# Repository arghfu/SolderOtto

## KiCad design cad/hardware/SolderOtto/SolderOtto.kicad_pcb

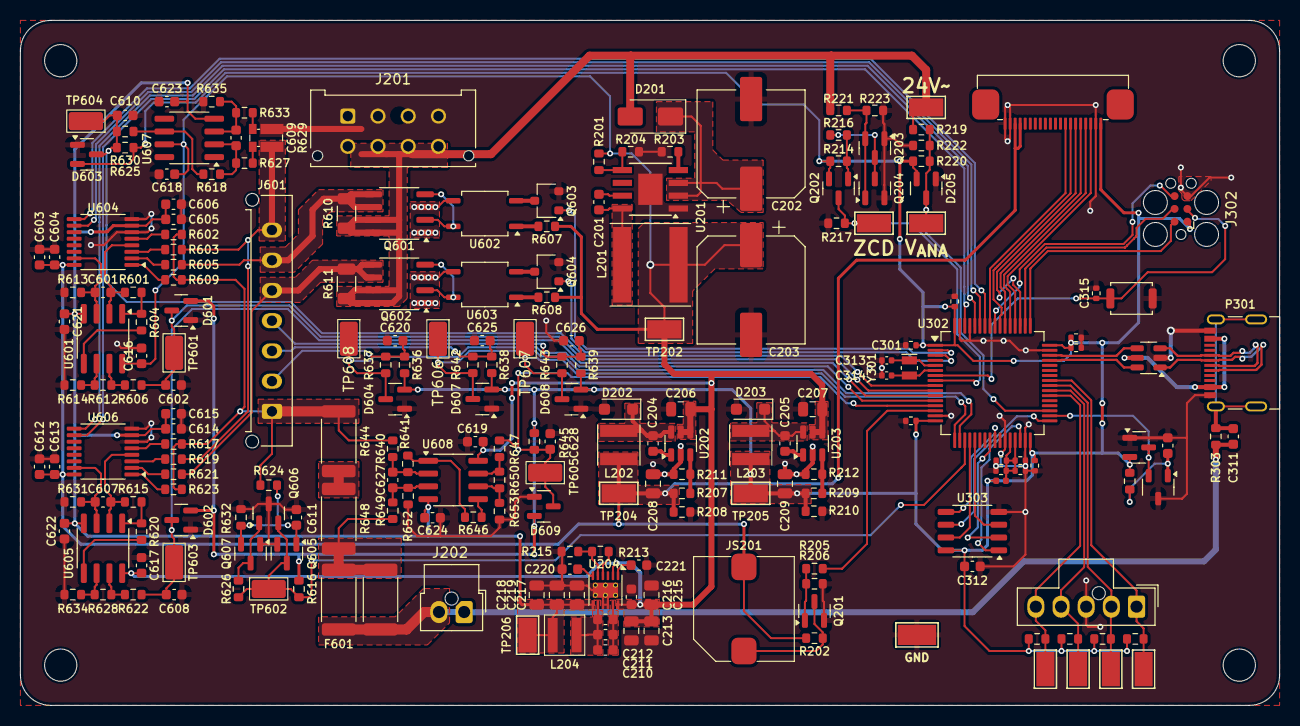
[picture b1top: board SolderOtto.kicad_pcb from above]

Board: 2 copper layers, 125.0 x 68.0 mm, 221 parts (0 on the bottom side), 127 nets.

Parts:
C201, C312, C603, C606, C612, C615, C616, C617, C618, C619, C620, C621, C622, C623, C624, C625, C626: 100n; C_0603_1608Metric
C202, C203: 100u; CP_Elec_10x10.5_A768
C204, C205, C311: 10n; C_0603_1608Metric
C206, C207: 10u; C_0805_2012Metric
C208, C209, C213, C214, C215, C217, C218, C219: 22u; C_0805_2012Metric
C210, C211, C212: 10u; C_0603_1608Metric
C216: 2u2; C_0603_1608Metric
C220, C222, C604, C605, C613, C614: 1u; C_0603_1608Metric
C221: 220n; C_0603_1608Metric
C301, C302, C303, C304, C305, C310, C315: 100n; R_0402_1005Metric
C306: 4u7; R_0402_1005Metric
C307: 10n; R_0402_1005Metric
C308, C309: 1u; R_0402_1005Metric
C313, C314: 9p; C_0402_1005Metric
C601, C607, C609, C627: 47p; C_0603_1608Metric
C602, C608, C610, C628: 1n; C_0603_1608Metric
C611: 100p; C_0603_1608Metric
D201: STPS2H100A; D_SMA
D202, D203: SMD16PL-TP; D_SOD-123F
D204, D205, D601, D602, D603, D604, D607, D608, D609: BAT54SFILM; SOT-23
F601: 1.25A; R_2512_6332Metric
J201: Conn_02x04_Counter_Clockwise; Molex_Micro-Fit_3.0_43045-0812_2x04_P3.00mm_Vertical
J202: Conn_01x02; Molex_Nano-Fit_105309-xx02_1x02_P2.50mm_Vertical
J302: Conn_ARM_SWD_TagConnect_TC2030; Tag-Connect_TC2030-IDC-FP_2x03_P1.27mm_Vertical
J401: Conn_01x20; FPC_BOTTOM_20POS_Würth_68712014522
J501: Conn_01x05; Molex_Nano-Fit_105309-xx05_1x05_P2.50mm_Vertical
J601: Conn_01x07; Molex_Micro-Fit_3.0_43650-0715_1x07_P3.00mm_Vertical
JS201: SMI-1027-T-5V-R
L201: 33u; L_Taiyo-Yuden_NR-80xx
L202, L203: 3u3; L_Taiyo-Yuden_NR-40xx
L204: 2u2; XFL4020
L301: 600R@100MHz; L_0402_1005Metric
P301: USB_C_Plug_USB2.0; USB_C_Receptacle_Molex_C_24P_SMD_RA
Q201: T2N7002AK; SOT-23
Q202, Q606: BC858B; SOT-23
Q203, Q204, Q605, Q607: BC847A; SOT-23
Q601, Q602: Q_Dual_NMOS; SO-8_3.9x4.9mm_P1.27mm
Q603, Q604: DTD123EK; SC-59
R201, R220, R222: 100k; R_0603_1608Metric
R202, R206, R501, R502, R503, R504, R636, R637, R638, R639, R642, R643: 4k7; R_0603_1608Metric
R203: 25k5; R_0603_1608Metric
R204: 14k3; R_0603_1608Metric
R205: 100; R_0603_1608Metric
R207, R209: 49k9; R_0603_1608Metric
R208, R210: 1k; R_0603_1608Metric
R211: 9k53; R_0603_1608Metric
R212: 16k2; R_0603_1608Metric
R213: 130k; R_0603_1608Metric
R214, R216, R217, R616, R646, R653: 10k; R_0603_1608Metric
R215: 24k; R_0603_1608Metric
R218: 200; R_0603_1608Metric
R219: 1M15; R_0603_1608Metric
R221: 22k; R_0603_1608Metric
R223, R303: 1M; R_0603_1608Metric
R601, R613, R615, R631: 590k; R_0603_1608Metric
R602, R603, R605, R609, R612, R617, R619, R621, R623, R628: 22k6; R_0603_1608Metric
R604, R614, R620, R634: 2k7; R_0603_1608Metric
R606, R622: 2k2; R_0603_1608Metric
R607, R608: 470; R_0603_1608Metric
R610, R611: 10M; R_1206_3216Metric
R618, R635: 453k; R_0603_1608Metric
R624: 470k; R_0603_1608Metric
R625, R630, R645, R647: 3k3; R_0603_1608Metric
R626, R632: 47k; R_0603_1608Metric
R627, R633: 20k; R_0603_1608Metric
R629: 5m; R_Shunt_Vishay_WSKW0612
R640, R649: 4k75; R_0603_1608Metric
R641, R652: 200k; R_0603_1608Metric
R644, R648: 220m; R_2512_6332Metric
R650: 187k; R_0603_1608Metric
R651: 1M; R_2512_6332Metric
SW301: SW_Push; SW_Push_SPST_NO_Alps_SKRK
TP201: 24V~; TestPoint_Keystone_5015_Micro-Minature
TP202: 12V; TestPoint_Keystone_5015_Micro-Minature
TP203: GND; TestPoint_Keystone_5019_Minature
TP204: 5V; TestPoint_Keystone_5015_Micro-Minature
TP205, TP206: 3V3; TestPoint_Keystone_5015_Micro-Minature
TP207: ZCD; TestPoint_Keystone_5015_Micro-Minature
TP208: V_{ANA}; TestPoint_Keystone_5015_Micro-Minature
TP501: EXT2; TestPoint_Keystone_5015_Micro-Minature
TP502: EXT3; TestPoint_Keystone_5015_Micro-Minature
TP503: EXT4; TestPoint_Keystone_5015_Micro-Minature
TP504: EXT5; TestPoint_Keystone_5015_Micro-Minature
TP601, TP602, TP603, TP606, TP607, TP608: T_{TIP}; TestPoint_Keystone_5015_Micro_Mini
TP604: I_{LOAD}; TestPoint_Keystone_5015_Micro_Mini
TP605: I_{LEAK}; TestPoint_Keystone_5015_Micro_Mini
U201: LMR38010; TI_SO-PowerPAD-8
U202, U203: AP3211K; SOT-23-6
U204: TPS63710; WSON-12-1EP_3x3mm_P0.5mm_EP1.5x2.5mm_ThermalVias
U205: MCP9701T-E/TT; SOT-23-3
U301: USBLC6-2SC6; SOT-23-6
U302: STM32G474RETx; LQFP-64_10x10mm_P0.5mm
U303: MX25R3235FM1xx0; SOP-8_3.9x4.9mm_P1.27mm
U601, U605, U608: OPA2186; SOIC-8_3.9x4.9mm_P1.27mm
U602, U603: VOM1271; SOP-4_3.8x4.1mm_P2.54mm
U604, U606: TMUX4053; TSSOP-16_4.4x5mm_P0.65mm
U607: OPA202; SOIC-8_3.9x4.9mm_P1.27mm
Y301: 32.768 kHz; Crystal_SMD_MicroCrystal_CC8V-T1A-2Pin_2.0x1.2mm

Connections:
24V_{AC}: D201.2 (A), J201.5, J201.6, J201.7, J201.8, Q601.7 (D), Q601.8 (D), Q602.7 (D), Q602.8 (D), R219.1, R221.1, R610.1, R611.1, TP201.1
+3V3: C209.2, C301.1, C302.1, C303.1, C304.1, C305.1, C306.1, C312.1, D204.2, D205.2, D601.2, D602.2, D603.2, D604.2, D607.2, D608.2, D609.2, J302.1 (VCC), J401.1, L203.2, L301.1, Q202.2 (E), R209.1, R210.1, R214.1, R218.2, R220.1, R501.1, R502.1, R503.1, R504.1, R616.2, R625.1, R636.1, R638.1, R639.1, R645.1, TP205.1, U302.1 (VBAT), U302.16 (VDD), U302.32 (VDD), U302.48 (VDD), U302.64 (VDD), U303.8 (VCC)
+5V: C208.2, C603.1, C604.1, C612.1, C613.1, J401.17, J401.18, JS201.2 (+), L202.2, R202.2, R207.1, R208.1, TP204.1, U604.16 (VCC), U606.16 (VCC)
+8V: C203.1, C206.1, C207.1, C213.2, C214.2, C215.2, C216.2, C616.1, C617.1, C618.1, C619.2, L201.2, R201.1, R607.1, R608.1, TP202.1, U202.4 (EN), U202.5 (IN), U203.4 (EN), U203.5 (IN), U204.2 (EN), U204.12 (VIN), U601.8 (V+), U605.8 (V+), U607.7 (V+), U608.8 (V+)
-5V: C217.2, C218.2, C219.2, C605.1, C606.1, C614.1, C615.1, C621.1, C622.1, C623.1, C624.1, L204.2, TP206.1, U204.7 (VOUT), U601.4 (V-), U604.7 (VEE), U605.4 (V-), U606.7 (VEE), U607.4 (V-), U608.4 (V-)
/Channel0/COM: J601.7, R603.1, R619.1, R629.1
/Channel0/DET: Q605.3 (C), Q606.2 (E), R616.1, R626.2, TP602.1, U302.19 (PA5)
/Channel0/I_{LEAK}: C628.1, D609.3, R645.2, R647.1, TP605.1, U302.13 (PA1)
/Channel0/I_{LOAD}: C610.1, D603.3, R625.2, R630.1, TP604.1, U302.9 (PC1)
/Channel0/LOAD: J601.6, Q601.5 (D), Q601.6 (D), R605.1, R610.2
/Channel0/LOAD0_SW: Q603.1 (B), U302.2 (PC13)
/Channel0/LOAD1_SW: Q604.1 (B), U302.3 (PC14)
/Channel0/SEL1_{a}: U302.58 (PB5), U604.9 (S1)
/Channel0/SEL1_{b}: U302.60 (PB7), U606.9 (S1)
/Channel0/SEL2_{a}: U302.59 (PB6), U604.10 (S2)
/Channel0/SEL2_{b}: U302.62 (PB9), U606.10 (S2)
/Channel0/TC: J601.1, R602.1, R609.1, R617.1, R623.1, R624.1, R640.1, R644.1
/Channel0/T_{TIP}_{a}: C602.1, D601.3, R606.2, TP601.1, U302.10 (PC2)
/Channel0/T_{TIP}_{b}: C608.1, D602.3, R622.2, TP603.1, U302.11 (PC3)
/Channel0/_handle_id: C620.1, J601.2, R636.2, R637.2
/Channel0/_iron_sense: J601.5, Q602.5 (D), Q602.6 (D), R611.2, R621.1
/Channel0/_stand_sense: C625.1, J601.3, R638.2, R642.2
/Channel0/_tip_change: C626.1, J601.4, R639.2, R643.2
/Channel0/handle_id: D604.3, R637.1, TP608.1, U302.12 (PA0)
/Channel0/stand_sense: D607.3, R642.1, TP606.1, U302.18 (PA4)
/Channel0/tip_change: D608.3, R643.1, TP607.1, U302.17 (PA3)
/Display/QSPI_CLK: J401.3, U302.52 (PC10)
/Display/QSPI_CS: J401.6, U302.51 (PA15)
/Display/SPI_MISO: J401.4, U302.53 (PC11)
/Display/SPI_MOSI: J401.5, U302.54 (PC12)
/Display/~INT: J401.7, U302.55 (PD2)
/Display/~PD: J401.8, U302.57 (PB4)
/External connection/EXT_0: J501.1, R501.2, TP501.1, U302.41 (PC9)
/External connection/EXT_1: J501.2, R502.2, TP502.1, U302.40 (PC8)
/External connection/EXT_2: J501.4, R503.2, TP503.1, U302.39 (PC7)
/External connection/EXT_3: J501.5, R504.2, TP504.1, U302.38 (PC6)
/Supply/Buzzer: R205.1, U302.14 (PA2)
/Supply/T_{AMB}: D204.3, U205.2 (Vout), U302.34 (PB12)
/Supply/V_{ANA}: D205.3, R219.2, R220.2, R222.1, TP208.1, U302.35 (PB13)
/Supply/ZCD: Q202.3 (C), R217.1, TP207.1, U302.8 (PC0)
/mcu/D+: U301.4 (I/O2), U302.46 (PA12)
/mcu/D-: U301.6 (I/O1), U302.45 (PA11)
/mcu/LSE_IN: C314.1, U302.6 (PF1), Y301.2
/mcu/LSE_OUT: C313.1, U302.5 (PF0), Y301.1
/mcu/QSPI_CLK: U302.30 (PB10), U303.6 (SCLK)
/mcu/QSPI_IO0: U302.25 (PB1), U303.5 (SI/SIO0)
/mcu/QSPI_IO1: U302.24 (PB0), U303.2 (SO/SIO1)
/mcu/QSPI_IO2: U302.21 (PA7), U303.3 (~WP/SIO2)
/mcu/QSPI_IO3: U302.20 (PA6), U303.7 (~RESET/SIO3)
/mcu/QSPI_NCS: U302.33 (PB11), U303.1 (~CS)
/mcu/SWDCLK: J302.4 (SWCLK), U302.50 (PA14)
/mcu/SWDIO: J302.2 (SWDIO), U302.49 (PA13)
/mcu/SWO: J302.6 (SWO), U302.56 (PB3)
/mcu/_D+: P301.A6 (D+), P301.B6 (D+), U301.3 (I/O2)
/mcu/_D-: P301.A7 (D-), P301.B7 (D-), U301.1 (I/O1)
/mcu/~RESET: C315.1, J302.3 (~RESET), SW301.2, U302.7 (PG10)
Earth: C311.1, F601.2, J202.1, J202.2, R303.2, R651.2
GND: C202.2, C203.2, C206.2, C207.2, C208.1, C209.1, C213.1, C214.1, C215.1, C216.1, C217.1, C218.1, C219.1, C220.1, C221.2, C222.2, C301.2, C302.2, C303.2, C304.2, C305.2, C306.2, C307.1, C308.2, C309.2, C310.2, C312.2, C313.2, C314.2, C315.2, C602.2, C603.2, C604.2, C605.2, C606.2, C608.2, C610.2, C611.2, C612.2, C613.2, C614.2, C615.2, C616.2, C617.2, C618.2, C619.1, C620.2, C621.2, C622.2, C623.2, C624.2, C625.2, C626.2, C628.2, D202.2 (A), D203.2 (A), D204.1, D205.1, D601.1, D602.1, D603.1, D604.1, D607.1, D608.1, D609.1, J201.1, J201.2, J201.3, J201.4, J302.5 (GND), J401.2, J401.19, J401.20, J501.3, P301.A1 (GND), P301.A12 (GND), P301.B1 (GND), P301.B12 (GND), Q201.2 (S), Q203.1 (B), Q204.2 (E), Q603.2 (E), Q604.2 (E), Q605.2 (E), Q606.3 (C), Q607.1 (B), R203.2, R204.2, R206.2, R208.2, R210.2, R211.2, R212.2, R215.2, R217.2, R222.2, R223.2, R613.2, R614.2, R629.4, R631.2, R632.1, R634.2, R635.1, R652.1, R653.1, SW301.1, TP203.1, U201.1 (GND), U201.9 (GND), U202.2 (GND), U203.2 (GND), U204.9 (GND), U204.10 (GND), U204.13 (GND), U205.3 (GND), U301.2 (GND), U302.15 (VSS), U302.27 (VSSA), U302.31 (VSS), U302.47 (VSS), U302.61 (PB8), U302.63 (VSS), U303.4 (GND), U604.6 (~E), U604.8 (GND), U606.6 (~E), U606.8 (GND)
unnamed: C202.1, D201.1 (K), U201.2 (EN), U201.3 (VIN)
unnamed: C204.2, D202.1 (K), L202.1, U202.6 (SW)
unnamed: C205.2, D203.1 (K), L203.1, U203.6 (SW)
unnamed: F601.1, R648.2, R649.2, R651.1
unnamed: JS201.1 (-), Q201.3 (D), R202.1
unnamed: C311.2, P301.S1 (SHIELD), R303.1
unnamed: Q201.1 (G), R205.2, R206.1
unnamed: Q202.1 (B), R214.2, R216.1
unnamed: Q203.3 (C), Q204.3 (C), R216.2
unnamed: Q203.2 (E), Q204.1 (B), R221.2, R223.1
unnamed: Q601.2 (G), Q601.4 (G), U602.4
unnamed: Q601.1 (S), Q601.3 (S), U602.3
unnamed: Q602.2 (G), Q602.4 (G), U603.4
unnamed: Q602.1 (S), Q602.3 (S), U603.3
unnamed: Q603.3 (C), U602.2
unnamed: Q604.3 (C), U603.2
unnamed: C611.1, Q605.1 (B), Q607.2 (E), R624.2, R632.2
unnamed: Q606.1 (B), Q607.3 (C), R626.1
unnamed: R601.2, R604.1, U601.1
unnamed: R606.1, R612.2, U601.7
unnamed: R607.2, U602.1
unnamed: R608.2, U603.1
unnamed: R615.2, R620.1, U605.1
unnamed: R618.2, R630.2, U607.6
unnamed: R622.1, R628.2, U605.7
unnamed: R627.1, R629.2
unnamed: R629.3, R633.1
unnamed: R641.2, R646.1, U608.1
unnamed: R644.2, R648.1
unnamed: R647.2, R650.2, U608.7
unnamed: C201.2, U201.7 (BOOT)
unnamed: R201.2, R204.1, U201.5 (FB)
unnamed: R203.1, U201.4 (RT/SYNC)
unnamed: C201.1, L201.1, U201.8 (SW)
unnamed: C204.1, U202.1 (BS)
unnamed: R207.2, R211.1, U202.3 (FB)
unnamed: C205.1, U203.1 (BS)
unnamed: R209.2, R212.1, U203.3 (FB)
unnamed: C220.2, U204.6 (CAP)
unnamed: C210.2, C211.2, C212.2, U204.11 (CP)
unnamed: R213.2, R215.1, U204.5 (FB)
unnamed: C210.1, C211.1, C212.1, L204.1, U204.8 (SW)
unnamed: C221.1, U204.1 (VAUX)
unnamed: R213.1, U204.4 (VREF)
unnamed: C222.1, R218.1, U205.1 (VDD)
unnamed: C601.2, R613.1, U601.3 (+), U604.15 (D2)
unnamed: C601.1, R601.1, U601.2 (-), U604.4 (D1)
unnamed: R604.2, U601.5 (+)
unnamed: R612.1, R614.1, U601.6 (-)
unnamed: R602.2, U604.5 (S1A)
unnamed: R603.2, U604.3 (S1B)
unnamed: R605.2, U604.2 (S2A)
unnamed: R609.2, U604.1 (S2B)
unnamed: C607.2, R631.1, U605.3 (+), U606.15 (D2)
unnamed: C607.1, R615.1, U605.2 (-), U606.4 (D1)
unnamed: R620.2, U605.5 (+)
unnamed: R628.1, R634.1, U605.6 (-)
unnamed: R617.2, U606.5 (S1A)
unnamed: R619.2, U606.3 (S1B)
unnamed: R621.2, U606.2 (S2A)
unnamed: R623.2, U606.1 (S2B)
unnamed: C609.2, R633.2, R635.2, U607.3 (+)
unnamed: C609.1, R618.1, R627.2, U607.2 (-)
unnamed: C627.2, R649.1, R652.2, U608.3 (+)
unnamed: C627.1, R640.2, R641.1, U608.2 (-)
unnamed: R646.2, U608.5 (+)
unnamed: R650.1, R653.2, U608.6 (-)
VBUS: P301.A4 (VBUS), P301.A9 (VBUS), P301.B4 (VBUS), P301.B9 (VBUS), U301.5 (VBUS)
VDDA: C307.2, C308.1, C309.1, C310.1, L301.2, U302.28 (VREF+), U302.29 (VDDA)

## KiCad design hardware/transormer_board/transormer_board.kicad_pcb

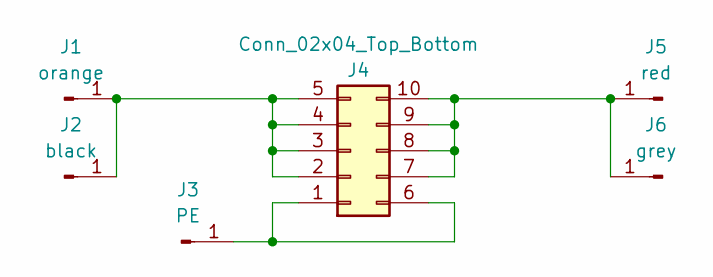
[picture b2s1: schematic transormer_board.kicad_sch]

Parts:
J1: orange; SolderWire-2.5sqmm_1x01_D2.4mm_OD3.6mm
J2: black; SolderWire-2.5sqmm_1x01_D2.4mm_OD3.6mm
J3: PE; flat_connector_4_75_mm
J4: Conn_02x04_Top_Bottom; Molex_Nano-Fit_105310-xx10_2x05_P2.50mm_Vertical
J5: red; SolderWire-2.5sqmm_1x01_D2.4mm_OD3.6mm
J6: grey; SolderWire-2.5sqmm_1x01_D2.4mm_OD3.6mm

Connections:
unnamed: J1.1, J2.1, J4.2, J4.3, J4.4, J4.5
unnamed: J3.1, J4.1, J4.6
unnamed: J4.7, J4.8, J4.9, J4.10, J5.1, J6.1

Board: 2 copper layers, 6 parts (0 on the bottom side), 3 nets, no tracks yet.

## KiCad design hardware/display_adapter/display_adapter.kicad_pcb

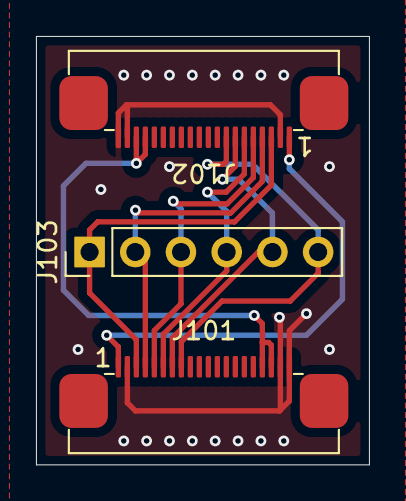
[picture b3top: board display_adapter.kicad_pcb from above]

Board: 2 copper layers, 18.5 x 23.8 mm, 3 parts (0 on the bottom side), 9 nets.

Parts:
J101, J102: Conn_01x20; FPC_BOTTOM_20POS_Würth_68712014522
J103: Conn_01x06; PinHeader_1x06_P2.54mm_Vertical

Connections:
+3V3: J101.1, J102.1
+5V: J101.17, J101.18, J102.17, J102.18
/QSPI_CLK: J101.3, J102.3, J103.1
/QSPI_CS: J101.6, J102.6, J103.4
/SPI_MISO: J101.4, J102.4, J103.2
/SPI_MOSI: J101.5, J102.5, J103.3
/~INT: J101.7, J102.7, J103.5
/~PD: J101.8, J102.8, J103.6
GND: J101.2, J101.19, J101.20, J102.2, J102.19, J102.20

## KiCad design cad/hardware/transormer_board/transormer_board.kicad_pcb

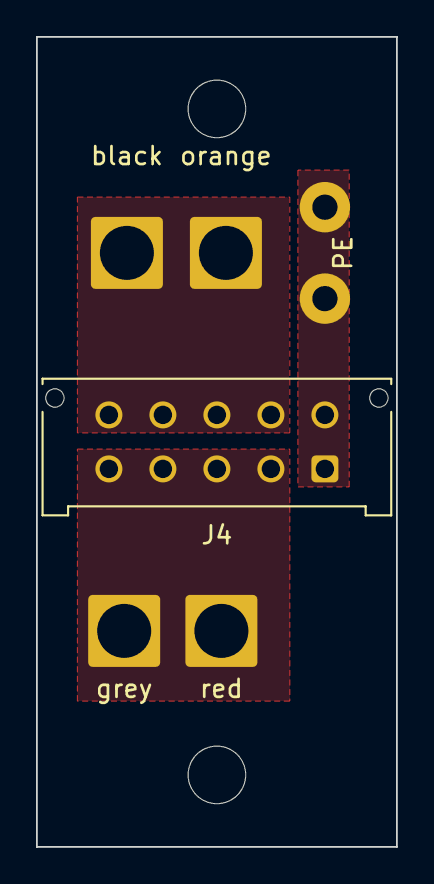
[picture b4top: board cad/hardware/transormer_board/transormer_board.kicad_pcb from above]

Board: 2 copper layers, 20.0 x 45.0 mm, 6 parts (0 on the bottom side), 3 nets, no tracks yet.

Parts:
J1: orange; SolderWire-2.5sqmm_1x01_D2.4mm_OD3.6mm
J2: black; SolderWire-2.5sqmm_1x01_D2.4mm_OD3.6mm
J3: PE; flat_connector_4_75_mm
J4: Conn_02x04_Top_Bottom; Molex_Micro-Fit_3.0_43045-1012_2x05_P3.00mm_Vertical
J5: red; SolderWire-2.5sqmm_1x01_D2.4mm_OD3.6mm
J6: grey; SolderWire-2.5sqmm_1x01_D2.4mm_OD3.6mm

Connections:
unnamed: J1.1, J2.1, J4.7, J4.8, J4.9, J4.10
unnamed: J3.1, J4.1, J4.6
unnamed: J4.2, J4.3, J4.4, J4.5, J5.1, J6.1

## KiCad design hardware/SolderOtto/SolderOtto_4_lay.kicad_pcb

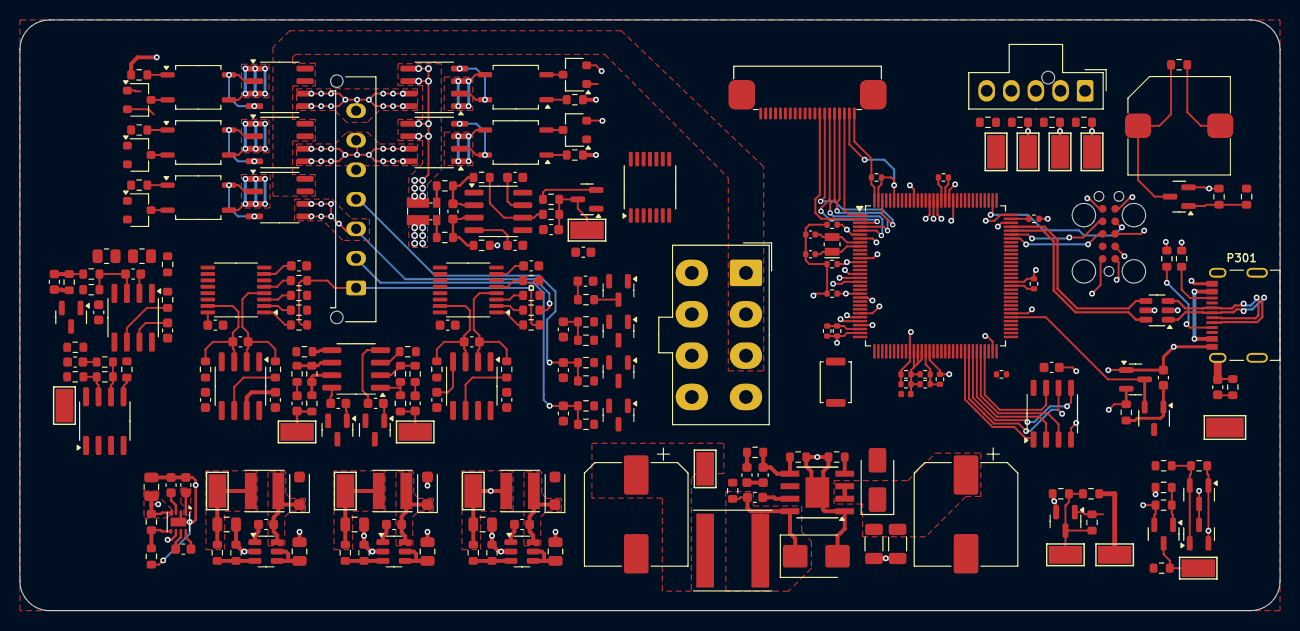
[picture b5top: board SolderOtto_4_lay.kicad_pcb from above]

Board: 4 copper layers, 128.0 x 60.0 mm, 232 parts (0 on the bottom side), 149 nets.

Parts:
C201: 3n3; C_0603_1608Metric
C202: 2n2; C_0603_1608Metric
C203, C206: 22u; CP_Elec_10x10
C204, C205: 2u2; C_1206_3216Metric
C207: 56p; C_0603_1608Metric
C208, C209, C210, C315: 10n; C_0603_1608Metric
C211, C212, C213, C219: 10u; C_0805_2012Metric
C214, C215, C216: 22u; C_0805_2012Metric
C217, C220: 4u7; C_0603_1608Metric
C218, C221, C905, C906, C919, C920: 1u; C_0603_1608Metric
C301, C302, C303, C304, C305, C306, C307, C308, C310, C314, C319: 100n; R_0402_1005Metric
C309: 4u7; R_0402_1005Metric
C311: 10n; R_0402_1005Metric
C312, C313: 1u; R_0402_1005Metric
C316, C601, C602, C603, C604, C701, C901, C904, C907, C910, C911, C914, C915, C918, C921, C922: 100n; C_0603_1608Metric
C317, C318: 9p; C_0402_1005Metric
C902, C908, C912, C916: 47p; C_0603_1608Metric
C903, C909, C913, C917: 1n; C_0603_1608Metric
D201: STPS2H100A; D_SMA
D202: B380B-13-F; D_SMB
D203, D204, D205: SMD16PL-TP; D_SOD-123F
D206, D207, D603, D604, D605, D606, D901, D902, D903, D904: BAT54SFILM; SOT-23
F901: 1.25A; Fuse_0603_1608Metric
J201: Conn_02x04_Counter_Clockwise; Molex_Mini-Fit_Jr_5566-08A_2x04_P4.20mm_Vertical
J301: TC-2050
J401: Conn_01x20; FPC_BOTTOM_20POS_Würth_68712014522
J501: Conn_01x05; Molex_Nano-Fit_105309-xx05_1x05_P2.50mm_Vertical
J601: Conn_01x07; Molex_Micro-Fit_3.0_43650-0715_1x07_P3.00mm_Vertical
JS201: SMI-1027-T-5V-R
L201: 33u; L_Taiyo-Yuden_NR-80xx
L202: 1u5; L_Taiyo-Yuden_NR-40xx
L203, L204: 3u3; L_Taiyo-Yuden_NR-40xx
L301: 600R@100MHz; L_0402_1005Metric
P301: USB_C_Plug_USB2.0; USB_C_Receptacle_Molex_C_24P_SMD_RA
Q201: T2N7002AK; SOT-23
Q202: BC858B; SOT-23
Q203, Q204: BC847A; SOT-23
Q801, Q802, Q803, Q807, Q808: Q_Dual_NMOS; SO-8_3.9x4.9mm_P1.27mm
Q804, Q805, Q806, Q809, Q810: DTD123EK; SC-59
R201, R202, R925, R931: 453k; R_0603_1608Metric
R203, R221, R223: 100k; R_0603_1608Metric
R204, R205, R206, R207: 49k9; R_0603_1608Metric
R208: 5k62; R_0603_1608Metric
R209: 9k53; R_0603_1608Metric
R210: 16k2; R_0603_1608Metric
R211: 215k; R_0603_1608Metric
R212, R216, R501, R502, R503, R504, R601, R602, R603, R604, R605, R606, R607: 4k7; R_0603_1608Metric
R213: 69k; R_0603_1608Metric
R214, R217, R218, R917, R924: 10k; R_0603_1608Metric
R215: 100; R_0603_1608Metric
R219: 200; R_0603_1608Metric
R220, R224, R303, R922: 1M; R_0603_1608Metric
R222: 22k; R_0603_1608Metric
R301, R302: 0; R_0603_1608Metric
R801, R802, R803, R804, R805: 470; R_0603_1608Metric
R901, R903, R911, R938: 590k; R_0603_1608Metric
R902, R905, R907, R908, R909, R910, R932, R934, R936, R937: 22k6; R_0603_1608Metric
R904, R912, R933, R939: 2k7; R_0603_1608Metric
R906, R935: 2k2; R_0603_1608Metric
R913, R923: 200k; R_0603_1608Metric
R914, R920: 4k75; R_0603_1608Metric
R915, R919: 220m; R_0805_2012Metric
R916, R918, R926, R929: 3k3; R_0603_1608Metric
R921: 187k; R_0603_1608Metric
R927, R930: 20k; R_0603_1608Metric
R928: 5m; R_Shunt_Vishay_WSKW0612
SW301: SW_Push; SW_Push_SPST_NO_Alps_SKRK
TP201: 24V~; TestPoint_Keystone_5015_Micro-Minature
TP202: 12V; TestPoint_Keystone_5015_Micro-Minature
TP203: GND; TestPoint_Keystone_5019_Minature
TP204: 8V; TestPoint_Keystone_5015_Micro-Minature
TP205: 5V; TestPoint_Keystone_5015_Micro-Minature
TP206: 3V3; TestPoint_Keystone_5015_Micro-Minature
TP207: ZCD; TestPoint_Keystone_5015_Micro-Minature
TP208: V_{ANA}; TestPoint_Keystone_5015_Micro-Minature
TP501: EXT2; TestPoint_Keystone_5015_Micro-Minature
TP502: EXT3; TestPoint_Keystone_5015_Micro-Minature
TP503: EXT4; TestPoint_Keystone_5015_Micro-Minature
TP504: EXT5; TestPoint_Keystone_5015_Micro-Minature
TP901, TP904: T_{TIP}; TestPoint_Keystone_5015_Micro-Minature
TP902: I_{LEAK}; TestPoint_Keystone_5015_Micro-Minature
TP903: I_{LOAD}; TestPoint_Keystone_5015_Micro-Minature
U201: LM5012; TI_SO-PowerPAD-8
U202, U203, U204: AP3211K; SOT-23-6
U205: LM27761; WSON-8-1EP_2x2mm_P0.5mm_EP0.9x1.6mm
U206: MCP9701T-E/TT; SOT-23-3
U301: USBLC6-2SC6; SOT-23-6
U302: STM32G474QETx; LQFP-128_14x14mm_P0.4mm
U303: MX25R3235FM1xx0; SOP-8_3.9x4.9mm_P1.27mm
U701: SN74LVC125A; TSSOP-14_4.4x5mm_P0.65mm
U801, U802, U803, U804, U805: VOM1271; SOP-4_3.8x4.1mm_P2.54mm
U901, U904, U905, U906: OPA202; SOIC-8_3.9x4.9mm_P1.27mm
U902, U907: LM358B; SOIC-8_3.9x4.9mm_P1.27mm
U903, U908: 74hc4053; TSSOP-16_4.4x5mm_P0.65mm
Y301: 32.768 kHz; Crystal_SMD_MicroCrystal_CC8V-T1A-2Pin_2.0x1.2mm

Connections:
24V_{AC}: D201.2 (A), J201.1, J201.2, J201.3, Q801.7 (D), Q801.8 (D), Q802.7 (D), Q802.8 (D), Q803.7 (D), Q803.8 (D), R220.1, R222.1, TP201.1
+3V3: C216.2, C301.1, C302.1, C303.1, C304.1, C305.1, C306.1, C307.1, C308.1, C309.1, C310.1, C316.1, C701.1, C905.1, C919.1, D206.2, D207.2, D603.2, D604.2, D605.2, D606.2, D901.2, D902.2, D903.2, D904.2, J301.1 (VCC), J401.1, L204.2, L301.1, Q202.2 (E), R207.1, R214.1, R219.2, R221.1, R501.1, R502.1, R503.1, R504.1, R601.1, R604.1, R605.1, R916.1, R926.1, TP206.1, U302.6 (VBAT), U302.13 (VDD), U302.31 (VDD), U302.47 (VDD), U302.64 (VDD), U302.79 (VDD), U302.95 (VDD), U302.111 (VDD), U302.128 (VDD), U303.8 (VCC), U701.14 (V_{CC}), U903.16 (VCC), U908.16 (VCC)
+5V: C215.2, C217.1, J401.17, J401.18, JS201.2 (+), L203.2, R206.1, R212.2, TP205.1, U205.1 (VIN), U205.6 (EN)
+8V: C214.2, C901.1, C907.1, C911.1, C915.1, C922.1, L202.2, R205.1, TP204.1, U901.7 (V+), U902.8 (V+), U904.7 (V+), U905.7 (V+), U906.7 (V+), U907.8 (V+)
+12V: C201.2, C206.1, C211.1, C212.1, C213.1, L201.2, R202.1, R801.1, R802.1, R803.1, R804.1, R805.1, TP202.1, U202.4 (EN), U202.5 (IN), U203.4 (EN), U203.5 (IN), U204.4 (EN), U204.5 (IN)
-5V: C219.1, C904.1, C906.1, C910.1, C914.1, C918.1, C920.1, C921.1, R211.1, U205.4 (VOUT), U901.4 (V-), U902.4 (V-), U903.7 (VEE), U904.4 (V-), U905.4 (V-), U906.4 (V-), U907.4 (V-), U908.7 (VEE)
/Channel0/COM: J601.7, Q802.5 (D), Q802.6 (D), Q808.7 (D), Q808.8 (D), R909.1, R932.1
/Channel0/COM_SW: U302.27 (PA0), U701.12 (A)
/Channel0/I_{LEAK}: C909.1, D902.3, R916.2, R918.1, TP902.1, U302.25 (PC3)
/Channel0/I_{LOAD}: C913.1, D903.3, R926.2, R929.1, TP903.1, U302.22 (PC0)
/Channel0/LOAD: J601.6, Q801.5 (D), Q801.6 (D), Q807.7 (D), Q807.8 (D), R905.1
/Channel0/LOAD0_SW: U302.28 (PA1), U701.5 (A)
/Channel0/LOAD1_SW: U302.29 (PA2), U701.9 (A)
/Channel0/LOW_SIDE_COM: Q810.1 (B), U302.32 (PA3), U701.13 (~OE)
/Channel0/LOW_SIDE_LOAD: Q809.1 (B), U302.26 (PF2), U701.4 (~OE), U701.10 (~OE)
/Channel0/SEL1: U302.16 (PF8), U903.9 (S3), U908.9 (S3)
/Channel0/SEL2: U302.17 (PF9), U903.10 (2S), U908.10 (2S)
/Channel0/TC: J601.1, R902.1, R907.1, R908.1, R914.1, R915.1, R936.1
/Channel0/_handle_id: C602.1, J601.2, R601.2, R603.2
/Channel0/_iron_sense: C601.1, J601.3, Q803.5 (D), Q803.6 (D), R602.2, R934.1
/Channel0/_stand_sense: C603.1, J601.5, R604.2, R606.2
/Channel0/_tip_change: C604.1, J601.4, R605.2, R607.2
/Channel0/channel_meas/CURRENT: Q807.5 (D), Q807.6 (D), Q808.5 (D), Q808.6 (D), R928.1
/Channel0/channel_meas/T_{TIP}_{a}: C903.1, D901.3, R906.2, TP901.1
/Channel0/channel_meas/T_{TIP}_{b}: C917.1, D904.3, R935.2, TP904.1
/Channel0/channel_power/COM_SW_HIGH: Q805.1 (B), U701.11 (Y)
/Channel0/channel_power/LOAD0_SW_HIGH: Q804.1 (B), U701.6 (Y)
/Channel0/channel_power/LOAD1_SW_HIGH: Q806.1 (B), U701.8 (Y)
/Channel0/handle_id: D604.3, R603.1, U302.23 (PC1)
/Channel0/iron_sense: D603.3, R602.1, U302.108 (PD0)
/Channel0/stand_sense: D605.3, R606.1, U302.66 (PB12)
/Channel0/tip_change: D606.3, R607.1, U302.103 (PG5)
/Display/QSPI_CLK: J401.3, U302.1 (PE2)
/Display/QSPI_CS: J401.6, U302.3 (PE4)
/Display/SPI_MISO: J401.4, U302.4 (PE5)
/Display/SPI_MOSI: J401.5, U302.5 (PE6)
/Display/~INT: J401.7, U302.126 (PE1)
/Display/~PD: J401.8, U302.2 (PE3)
/External connection/EXT_0: J501.1, R501.2, TP501.1, U302.112 (PD2)
/External connection/EXT_1: J501.2, R502.2, TP502.1, U302.113 (PD3)
/External connection/EXT_2: J501.4, R503.2, TP503.1, U302.114 (PD4)
/External connection/EXT_3: J501.5, R504.2, TP504.1, U302.115 (PD5)
/Supply/Buzzer: R215.1, U302.7 (PC13)
/Supply/T_{AMB}: D206.3, U206.2 (Vout), U302.70 (PD8)
/Supply/V_{ANA}: D207.3, R220.2, R221.2, R223.1, TP208.1, U302.71 (PD9)
/Supply/ZCD: Q202.3 (C), R218.1, TP207.1, U302.125 (PE0)
/mcu/D+: U301.4 (I/O2), U302.93 (PA12)
/mcu/D-: U301.6 (I/O1), U302.92 (PA11)
/mcu/DBG_RX: J301.7 (RXD), R302.1, U302.91 (PA10)
/mcu/DBG_TX: J301.8 (TXD), R301.1, U302.90 (PA9)
/mcu/LSE_IN: C318.1, U302.8 (PC14), Y301.2
/mcu/LSE_OUT: C317.1, U302.9 (PC15), Y301.1
/mcu/QSPI_CLK: U302.56 (PE10), U303.1 (~CS)
/mcu/QSPI_IO0: U302.58 (PE12), U303.5 (SI/SIO0)
/mcu/QSPI_IO1: U302.59 (PE13), U303.2 (SO/SIO1)
/mcu/QSPI_IO2: U302.60 (PE14), U303.3 (~WP/SIO2)
/mcu/QSPI_IO3: U302.61 (PE15), U303.7 (~RESET/SIO3)
/mcu/QSPI_NCS: U302.57 (PE11), U303.6 (SCLK)
/mcu/SWDCLK: J301.4 (SWCLK), U302.98 (PA14)
/mcu/SWDIO: J301.2 (SWDIO), U302.96 (PA13)
/mcu/SWO: J301.6 (SWO), U302.118 (PB3)
/mcu/_D+: P301.A6 (D+), P301.B6 (D+), U301.3 (I/O2)
/mcu/_D-: P301.A7 (D-), P301.B7 (D-), U301.1 (I/O1)
/mcu/~RESET: C319.1, J301.10 (RESET), SW301.2, U302.21 (PG10)
Earth: C315.1, F901.2, J201.4, J201.8, R303.2, R922.2
GND: C203.2, C204.2, C205.2, C206.2, C211.2, C212.2, C213.2, C214.1, C215.1, C216.1, C217.2, C219.2, C220.2, C221.2, C301.2, C302.2, C303.2, C304.2, C305.2, C306.2, C307.2, C308.2, C309.2, C310.2, C311.1, C312.2, C313.2, C314.2, C316.2, C317.2, C318.2, C319.2, C601.2, C602.2, C603.2, C604.2, C701.2, C901.2, C903.2, C904.2, C905.2, C906.2, C907.2, C909.2, C910.2, C911.2, C913.2, C914.2, C915.2, C917.2, C918.2, C919.2, C920.2, C921.2, C922.2, D202.2 (A), D203.2 (A), D204.2 (A), D205.2 (A), D206.1, D207.1, D603.1, D604.1, D605.1, D606.1, D901.1, D902.1, D903.1, D904.1, J201.5, J201.6, J201.7, J301.3 (GND), J301.5 (GND), J401.2, J401.19, J401.20, J501.3, P301.A1 (GND), P301.A12 (GND), P301.B1 (GND), P301.B12 (GND), Q201.2 (S), Q203.1 (B), Q204.2 (E), Q804.2 (E), Q805.2 (E), Q806.2 (E), Q809.2 (E), Q810.2 (E), R203.2, R204.2, R208.2, R209.2, R210.2, R213.2, R216.2, R218.2, R223.2, R224.2, R911.2, R912.2, R923.2, R924.1, R928.4, R931.1, R938.2, R939.2, SW301.1, TP203.1, U201.1 (GND), U201.9 (EP), U202.2 (GND), U203.2 (GND), U204.2 (GND), U205.2 (GND), U205.9 (PAD), U206.3 (GND), U301.2 (GND), U302.12 (VSS), U302.30 (VSS), U302.42 (VSSA), U302.46 (VSS), U302.63 (VSS), U302.78 (VSS), U302.94 (VSS), U302.110 (VSS), U302.123 (PB8), U302.127 (VSS), U303.4 (GND), U701.7 (GND), U903.6 (~E), U903.8 (GND), U908.6 (~E), U908.8 (GND)
unnamed: C201.1, C207.1, R201.1
unnamed: C203.1, C204.1, C205.1, D201.1 (K), U201.2 (VIN), U201.3 (EN)
unnamed: C202.1, D202.1 (K), L201.1, R201.2, U201.8 (SW)
unnamed: C209.2, D203.1 (K), L203.1, U203.6 (SW)
unnamed: C210.2, D204.1 (K), L204.1, U204.6 (SW)
unnamed: C208.2, D205.1 (K), L202.1, U202.6 (SW)
unnamed: F901.1, R919.2, R920.2, R922.1
unnamed: JS201.1 (-), Q201.3 (D), R212.1
unnamed: P301.A5 (CC1), R301.2
unnamed: P301.B5 (CC2), R302.2
unnamed: C315.2, P301.S1 (SHIELD), R303.1
unnamed: Q201.1 (G), R215.2, R216.1
unnamed: Q202.1 (B), R214.2, R217.1
unnamed: Q203.3 (C), Q204.3 (C), R217.2
unnamed: Q203.2 (E), Q204.1 (B), R222.2, R224.1
unnamed: Q801.2 (G), Q801.4 (G), U801.4
unnamed: Q801.1 (S), Q801.3 (S), U801.3
unnamed: Q802.2 (G), Q802.4 (G), U802.4
unnamed: Q802.1 (S), Q802.3 (S), U802.3
unnamed: Q803.2 (G), Q803.4 (G), U803.4
unnamed: Q803.1 (S), Q803.3 (S), U803.3
unnamed: Q804.3 (C), U801.2
unnamed: Q805.3 (C), U802.2
unnamed: Q806.3 (C), U803.2
unnamed: Q807.2 (G), Q807.4 (G), U804.4
unnamed: Q807.1 (S), Q807.3 (S), U804.3
unnamed: Q808.2 (G), Q808.4 (G), U805.4
unnamed: Q808.1 (S), Q808.3 (S), U805.3
unnamed: Q809.3 (C), U804.2
unnamed: Q810.3 (C), U805.2
unnamed: R801.2, U801.1
unnamed: R802.2, U802.1
unnamed: R803.2, U803.1
unnamed: R804.2, U804.1
unnamed: R805.2, U805.1
unnamed: R901.2, R904.1, U901.6
unnamed: R903.2, R933.1, U906.6
unnamed: R906.1, R910.2, U902.7
unnamed: R913.2, R917.1, U904.6
unnamed: R915.2, R919.1
unnamed: R918.2, R921.2, U907.7
unnamed: R925.2, R929.2, U905.6
unnamed: R927.1, R928.2
unnamed: R928.3, R930.1
unnamed: R935.1, R937.2, U902.1
unnamed: C202.2, U201.7 (BST)
unnamed: C207.2, R202.2, R204.1, U201.5 (FB)
unnamed: R203.1, U201.4 (RON)
unnamed: C208.1, U202.1 (BS)
unnamed: R205.2, R208.1, U202.3 (FB)
unnamed: C209.1, U203.1 (BS)
unnamed: R206.2, R209.1, U203.3 (FB)
unnamed: C210.1, U204.1 (BS)
unnamed: R207.2, R210.1, U204.3 (FB)
unnamed: C218.1, U205.8 (C+)
unnamed: C218.2, U205.7 (C-)
unnamed: C220.1, U205.3 (CPOUT)
unnamed: R211.2, R213.1, U205.5 (VFB)
unnamed: C221.1, R219.1, U206.1 (VDD)
unnamed: C902.2, R911.1, U901.3 (+), U903.15 (2Z)
unnamed: C902.1, R901.1, U901.2 (-), U903.4 (3Z)
unnamed: R933.2, U902.3 (+)
unnamed: R937.1, R939.1, U902.2 (-)
unnamed: R904.2, U902.5 (+)
unnamed: R910.1, R912.1, U902.6 (-)
unnamed: R905.2, U903.2 (2Y0)
unnamed: R902.2, U903.1 (2Y1)
unnamed: R908.2, U903.5 (3Y0)
unnamed: R909.2, U903.3 (3Y1)
unnamed: C908.2, R920.1, R923.1, U904.3 (+)
unnamed: C908.1, R913.1, R914.2, U904.2 (-)
unnamed: C912.2, R930.2, R931.2, U905.3 (+)
unnamed: C912.1, R925.1, R927.2, U905.2 (-)
unnamed: C916.2, R938.1, U906.3 (+), U908.15 (2Z)
unnamed: C916.1, R903.1, U906.2 (-), U908.4 (3Z)
unnamed: R917.2, U907.5 (+)
unnamed: R921.1, R924.2, U907.6 (-)
unnamed: R934.2, U908.2 (2Y0)
unnamed: R936.2, U908.1 (2Y1)
unnamed: R907.2, U908.5 (3Y0)
unnamed: R932.2, U908.3 (3Y1)
VBUS: P301.A4 (VBUS), P301.A9 (VBUS), P301.B4 (VBUS), P301.B9 (VBUS), U301.5 (VBUS)
VDDA: C311.2, C312.1, C313.1, C314.1, L301.2, U302.43 (VREF+), U302.44 (VREF_+), U302.45 (VDDA)

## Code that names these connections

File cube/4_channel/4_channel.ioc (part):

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Mcu.Name=STM32G474Q(B-C-E)Tx
Mcu.Package=LQFP128
Mcu.UserName=STM32G474QETx
PA0.Mode=IN1-Single-Ended
PA0.Signal=ADC1_IN1
PA10.Mode=Asynchronous
PA10.Signal=USART1_RX
PA11.Mode=Device
PA11.Signal=USB_DM
PA12.Mode=Device
PA12.Signal=USB_DP
PA13.Mode=Trace_Asynchronous_SW
PA13.Signal=SYS_JTMS-SWDIO
PA14.Mode=Trace_Asynchronous_SW
PA14.Signal=SYS_JTCK-SWCLK
PA15.Signal=GPIO_Output
PA4.Mode=IN17-Single-Ended
PA4.Signal=ADC2_IN17
PA5.Mode=IN13-Single-Ended
PA5.Signal=ADC2_IN13
PA6.Mode=IN3-Single-Ended
PA6.Signal=ADC2_IN3
PA7.Mode=IN4-Single-Ended
PA7.Signal=ADC2_IN4
PA8.Signal=GPIO_Output
PA9.Mode=Asynchronous
PA9.Signal=USART1_TX
PB0.Signal=GPIO_Output
PB1.Signal=GPIO_Output
PB10.Signal=GPIO_Output
PB11.Signal=GPIO_Output
PB12.Signal=GPXTI12
PB13.Signal=GPXTI13
PB14.Signal=GPXTI14
PB15.Signal=GPXTI15
PB2.Signal=GPIO_Output
PB3.Mode=Trace_Asynchronous_SW
PB3.Signal=SYS_JTDO-SWO
PB4.Signal=GPIO_Input
PB5.Signal=GPIO_Input
PB6.Signal=GPIO_Input
PB7.Signal=GPIO_Input
PB9.Signal=GPIO_Input
PC0.Mode=IN6-Single-Ended
PC0.Signal=ADC1_IN6
PC1.Mode=IN7-Single-Ended
PC1.Signal=ADC1_IN7
PC10.Signal=GPIO_Output
PC11.Signal=GPIO_Output
PC12.Signal=GPIO_Output
PC13.Signal=GPIO_Output
PC14-OSC32_IN.Mode=LSE-External-Oscillator
PC14-OSC32_IN.Signal=RCC_OSC32_IN
PC15-OSC32_OUT.Mode=LSE-External-Oscillator
PC15-OSC32_OUT.Signal=RCC_OSC32_OUT
PC2.Mode=IN8-Single-Ended
PC2.Signal=ADC1_IN8
PC3.Mode=IN9-Single-Ended
PC3.Signal=ADC1_IN9
PC5.Signal=GPIO_Output
PC6.Signal=GPIO_Output
PC7.Signal=GPIO_Output
PC8.Signal=GPIO_Output
PC9.Signal=GPIO_Output
PD0.Signal=GPIO_Input
PD1.Signal=GPIO_Input
PD10.Mode=IN7-Single-Ended
PD10.Signal=ADC3_IN7
PD11.Mode=IN8-Single-Ended
PD11.Signal=ADC4_IN8
PD12.Mode=IN9-Single-Ended
PD12.Signal=ADC4_IN9
PD13.Mode=IN10-Single-Ended
PD13.Signal=ADC4_IN10
PD14.Mode=IN11-Single-Ended
PD14.Signal=ADC4_IN11
PD15.Signal=GPIO_Output
PD2.Signal=GPXTI2
PD3.Signal=GPXTI3
PD4.Signal=GPXTI4
PD5.Signal=GPIO_Output
PD6.Signal=GPIO_Output
PD7.Signal=GPIO_Output
PD8.Mode=IN12-Single-Ended
PD8.Signal=ADC5_IN12
PD9.Mode=IN13-Single-Ended
PD9.Signal=ADC5_IN13
PE1.Signal=GPXTI1
PE10.Mode=Single Bank 1
PE10.Signal=QUADSPI1_CLK
PE11.Mode=Single Bank 1
PE11.Signal=QUADSPI1_BK1_NCS
PE12.Mode=Single Bank 1
PE12.Signal=QUADSPI1_BK1_IO0
PE13.Mode=Single Bank 1
PE13.Signal=QUADSPI1_BK1_IO1
PE14.Mode=Single Bank 1
PE14.Signal=QUADSPI1_BK1_IO2
PE15.Mode=Single Bank 1
PE15.Signal=QUADSPI1_BK1_IO3
PE2.Mode=Full_Duplex_Master
PE2.Signal=SPI4_SCK
PE3.Signal=GPIO_Output
PE4.Mode=NSS_Signal_Hard_Output
PE4.Signal=SPI4_NSS
PE5.Mode=Full_Duplex_Master
PE5.Signal=SPI4_MISO
PE6.Mode=Full_Duplex_Master
PE6.Signal=SPI4_MOSI
PE7.Mode=IN4-Single-Ended
PE7.Signal=ADC3_IN4
PE8.Mode=IN6-Single-Ended
PE8.Signal=ADC3_IN6
PE9.Mode=IN2-Single-Ended
PE9.Signal=ADC3_IN2
PF0-OSC_IN.Signal=GPIO_Output
PF10.Signal=GPIO_Output
PF3.Signal=GPIO_Output
PF4.Signal=GPIO_Output
PF5.Signal=GPIO_Output
PF6.Signal=GPIO_Output
PF7.Signal=GPIO_Output
PF8.Signal=GPIO_Output
PF9.Signal=GPIO_Output
PG0.Signal=GPXTI0
PG2.Signal=GPIO_Output
PG3.Signal=GPIO_Output
PG4.Signal=GPIO_Output
PG5.Signal=GPXTI5
PG6.Signal=GPXTI6
PG7.Signal=GPXTI7
PG8.Signal=GPXTI8
PG9.Signal=GPIO_Input
RCC.HSE_VALUE=8000000
RCC.SYSCLKFreq_VALUE=160000000
RCC.SYSCLKSource=RCC_SYSCLKSOURCE_PLLCLK
board=custom

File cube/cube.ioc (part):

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Mcu.Name=STM32G474R(B-C-E)Tx
Mcu.Package=LQFP64
Mcu.UserName=STM32G474RETx
PA0.Mode=IN1-Single-Ended
PA0.Signal=ADC1_IN1
PA1.Signal=ADC1_IN2
PA11.Mode=Device
PA11.Signal=USB_DM
PA12.Mode=Device
PA12.Signal=USB_DP
PA13.Mode=Trace_Asynchronous_SW
PA13.Signal=SYS_JTMS-SWDIO
PA14.Mode=Trace_Asynchronous_SW
PA14.Signal=SYS_JTCK-SWCLK
PA15.Mode=NSS_Signal_Hard_Output
PA15.Signal=SPI3_NSS
PA2.Signal=GPIO_Output
PA3.Signal=GPXTI3
PA4.Signal=GPXTI4
PA5.Signal=GPXTI5
PA6.Mode=Single Bank 1
PA6.Signal=QUADSPI1_BK1_IO3
PA7.Mode=Single Bank 1
PA7.Signal=QUADSPI1_BK1_IO2
PB0.Mode=Single Bank 1
PB0.Signal=QUADSPI1_BK1_IO1
PB1.Mode=Single Bank 1
PB1.Signal=QUADSPI1_BK1_IO0
PB10.Mode=Single Bank 1
PB10.Signal=QUADSPI1_CLK
PB11.Mode=Single Bank 1
PB11.Signal=QUADSPI1_BK1_NCS
PB14.Mode=IN4-Differential
PB14.Signal=ADC4_IN4
PB15.Mode=IN4-Differential
PB15.Signal=ADC4_IN5
PB3.Mode=Trace_Asynchronous_SW
PB3.Signal=SYS_JTDO-SWO
PB4.GPIOParameters=GPIO_Label
PB4.GPIO_Label=DISP_PD
PB4.Signal=GPIO_Output
PC0.GPIOParameters=GPIO_Label
PC0.GPIO_Label=ZCD
PC0.Signal=GPXTI0
PC1.Mode=IN7-Differential
PC1.Signal=ADC1_IN7
PC10.Mode=Full_Duplex_Master
PC10.Signal=SPI3_SCK
PC11.Mode=Full_Duplex_Master
PC11.Signal=SPI3_MISO
PC12.Mode=Full_Duplex_Master
PC12.Signal=SPI3_MOSI
PC13.Signal=GPIO_Output
PC14-OSC32_IN.Signal=GPIO_Output
PC2.Mode=IN7-Differential
PC2.Signal=ADC1_IN8
PC3.Mode=IN9-Single-Ended
PC3.Signal=ADC1_IN9
PC6.Signal=GPIO_Output
PC7.Signal=GPIO_Output
PC8.Signal=GPIO_Output
PC9.Signal=GPIO_Output
PD2.Signal=GPXTI2
PF0-OSC_IN.Mode=HSE-External-Oscillator
PF0-OSC_IN.Signal=RCC_OSC_IN
PF1-OSC_OUT.Mode=HSE-External-Oscillator
PF1-OSC_OUT.Signal=RCC_OSC_OUT
RCC.HSE_VALUE=8000000
RCC.SYSCLKFreq_VALUE=16000000
board=custom

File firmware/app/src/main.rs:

#![no_std]
#![no_main]
#![allow(dead_code)]
#![allow(unused_imports)]
use assign_resources::assign_resources;
use embassy_stm32::Peri;

use core::iter::IntoIterator;
use core::ops::DerefMut;
use cortex_m_rt::entry;
use panic_probe as _;
#[cfg(feature = "defmt")]
use {defmt::*, defmt_rtt as _};

use embassy_executor::{Executor, InterruptExecutor};
use embassy_futures::select::{select, select3, Either, Either3};
use embassy_stm32::adc::{Adc, AdcChannel, AnyAdcChannel, SampleTime};
use embassy_stm32::dma::WritableRingBuffer;
use embassy_stm32::exti::ExtiInput;
use embassy_stm32::gpio::{Level, Output, OutputOpenDrain, Pull, Speed};
use embassy_stm32::interrupt::{InterruptExt, Priority};
use embassy_stm32::peripherals::{ADC1, DMA1, DMA1_CH1};
use embassy_stm32::Config;
use embassy_stm32::{interrupt, peripherals};
use embassy_sync::blocking_mutex::raw::CriticalSectionRawMutex;
use embassy_sync::channel::{Channel, Sender};
use embassy_sync::mutex;
use embassy_time::{Duration, Ticker, Timer};
use heapless::Vec;
use static_cell::StaticCell;
mod dfu;
mod solderotto;
use solderotto::control::*;
use solderotto::*;

enum DebugState {
    Toggle,
}

type TipAdcAsyncMutex = mutex::Mutex<CriticalSectionRawMutex, TipAdc<'static, ADC1, DMA1_CH1>>;
type DebugChannel = Channel<CriticalSectionRawMutex, DebugState, 64>;

static EXECUTOR_HI: InterruptExecutor = InterruptExecutor::new();
static EXECUTOR_LOW: StaticCell<Executor> = StaticCell::new();

static CHANNEL: DebugChannel = Channel::new();

assign_resources! {
    dfu: DfuResources {
        dp: PA12,
        dm: PA11,
        usb: USB,
        flash: FLASH,
    }

    ext: SysResource {
        ext3: PC6,
        ext2: PC7,
        ext1: PC8,
        ext0: PC9,
    }

    zcd: ZcdResources {
        zcd: PC0,
        int: EXTI0,
    }

    driver: OutputResource {
        high_side_com: PC13,
        low_side_com: PF5,
        high_side_load0: PF3,
        high_side_load1: PF4,
        low_side_load: PF7,
    }

    temp: TempResources {
        tip0: PC2,
        tip1: PC3,
    }

    tip_adc: TipAdcResources {
        adc: ADC1,
        dma: DMA1_CH1,
    }
}

#[inline]
fn calc_temp(adc: u16) -> f32 {
    let adc = adc as f32;
    4.30767839e-06 * adc * adc + 1.15134114e-01 * adc + 33.1575698
}

#[interrupt]
unsafe fn I2C1_EV() {
    EXECUTOR_HI.on_interrupt()
}

#[embassy_executor::task]
async fn zero_crossing(
    tip_adc: &'static TipAdcAsyncMutex,
    dbg_control: Sender<'static, CriticalSectionRawMutex, DebugState, 64>,
    zcd: ZcdResources,
    temp: TempResources,
    driver: OutputResource,
) {
    let mut read_buffer: [u16; 2] = [0; 2];
    let mut control = WaveControl::new(driver, 1000);

    let mut set_point = 2;
    let mut dur: Duration = Duration::default();

    // control.set_point(set_point);

    let mut zcd = ExtiInput::new(zcd.zcd, zcd.int, Pull::None);
    let mut tip0 = AdcChannel::degrade_adc(temp.tip0);
    let mut tip1 = AdcChannel::degrade_adc(temp.tip1);

    let mut foo = Ticker::every(Duration::from_secs(1));
    let mut bar = Ticker::every(Duration::from_secs(60));

    loop {
        match select3(zcd.wait_for_any_edge(), foo.next(), bar.next()).await {
            Either3::First(_) => match zcd.get_level() {
                Level::Low => {
                    let now = embassy_time::Instant::now();
                    {
                        dbg_control.send(DebugState::Toggle).await;
                        let mut locked_adc = tip_adc.lock().await;
                        let tip_adc = locked_adc.deref_mut();

                        tip_adc
                            .adc
                            .read(
                                tip_adc.dma.reborrow(),
                                [
                                    (&mut tip0, SampleTime::CYCLES247_5),
                                    (&mut tip1, SampleTime::CYCLES247_5),
                                ]
                                .into_iter(),
                                &mut read_buffer,
                            )
                            .await;
                    }
                    dur = embassy_time::Instant::now().duration_since(now);
                }
                Level::High => {
                    // control.drive_high(BridgeState::Load);
                    dbg_control.send(DebugState::Toggle).await;
                }
            },
            Either3::Second(_) => {
                info!("tip0: {:?}", calc_temp(read_buffer[0]));
                info!("tip1: {:?}", calc_temp(read_buffer[1]));
            }
            Either3::Third(_) => {
                // if set_point > 40 {
                //     set_point = 0;
                // }
                // set_point += 1;
                // control.set_point(set_point);

                info!("adjust setpoint to {}", set_point);
            }
        }
    }
}

#[embassy_executor::task]
async fn debug_task(ext: SysResource) {
    let mut dbg0 = OutputOpenDrain::new(ext.ext0, Level::Low, Speed::Low);
    // let mut dbg1 = OutputOpenDrain::new(ext.ext1, Level::Low, Speed::Low);
    // let mut dbg2 = OutputOpenDrain::new(ext.ext2, Level::Low, Speed::Low);
    // let mut dbg3 = OutputOpenDrain::new(ext.ext3, Level::Low, Speed::Low);

    loop {
        match CHANNEL.receive().await {
            DebugState::Toggle => {
                dbg0.toggle();
            }
        }
    }
}

#[entry]
fn main() -> ! {
    #[cfg(feature = "defmt")]
    info!("Hello, World!");

    let mut config = Config::default();
    {
        use embassy_stm32::rcc::*;
        config.rcc.hsi = true;
        config.rcc.pll = Some(Pll {
            source: PllSource::HSI,
            prediv: PllPreDiv::DIV1,
            mul: PllMul::MUL20,
            // Main system clock at 160 MHz
            divr: Some(PllRDiv::DIV2),
            divq: Some(PllQDiv::DIV8),
            divp: Some(PllPDiv::DIV2),
        });
        config.rcc.mux.adc12sel = mux::Adcsel::SYS;
        config.rcc.mux.adc345sel = mux::Adcsel::SYS;
        config.rcc.sys = Sysclk::PLL1_R;
    }

    let p = embassy_stm32::init(config);
    let r = split_resources!(p);

    static ADC: StaticCell<TipAdcAsyncMutex> = StaticCell::new();
    let adc = ADC.init(mutex::Mutex::new(TipAdc::new(r.tip_adc.adc, r.tip_adc.dma)));

    let sel1_a = Output::new(p.PF8, Level::Low, Speed::Low);
    let sel2_a = Output::new(p.PF10, Level::Low, Speed::Low);

    let sel1_b = Output::new(p.PF9, Level::Low, Speed::Low);
    let sel2_b = Output::new(p.PF0, Level::Low, Speed::Low);

    let spawner = EXECUTOR_HI.start(interrupt::I2C1_EV);
    spawner
        .spawn(zero_crossing(
            adc,
            CHANNEL.sender(),
            r.zcd,
            r.temp,
            r.driver,
        ))
        .unwrap();

    let executor = EXECUTOR_LOW.init(Executor::new());
    executor.run(|spawner| {
        // spawner.spawn(check_connection(adc)).unwrap();
        spawner.spawn(dfu::dfu(r.dfu)).unwrap();
        spawner.spawn(debug_task(r.ext)).unwrap();
    });
}
